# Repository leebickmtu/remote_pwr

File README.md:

Remote Power (RPi HAT)
=========================
Remotely query/change the power state of a computer from an always on, low power Raspberry Pi.

Intended to be used over SSH to control the power state of a desktop computer.

Includes EAGLE board schematic for a RPi Zero HAT which the computer's front panel header connect to. And python scripts which can then be executed on the RPi to query/change the power state of the connected computer.

EAGLE board and schematic
--------

Python script use
--------
```bash
# Query the power state (returns 'sleep', 'on', 'off')
./remote_pwr state

# "Push" the power or reset buttons
./remote_pwr pulse pwr
./remote_pwr pulse rst

# "Hold" the power button
./remote_pwr hold pwr
```

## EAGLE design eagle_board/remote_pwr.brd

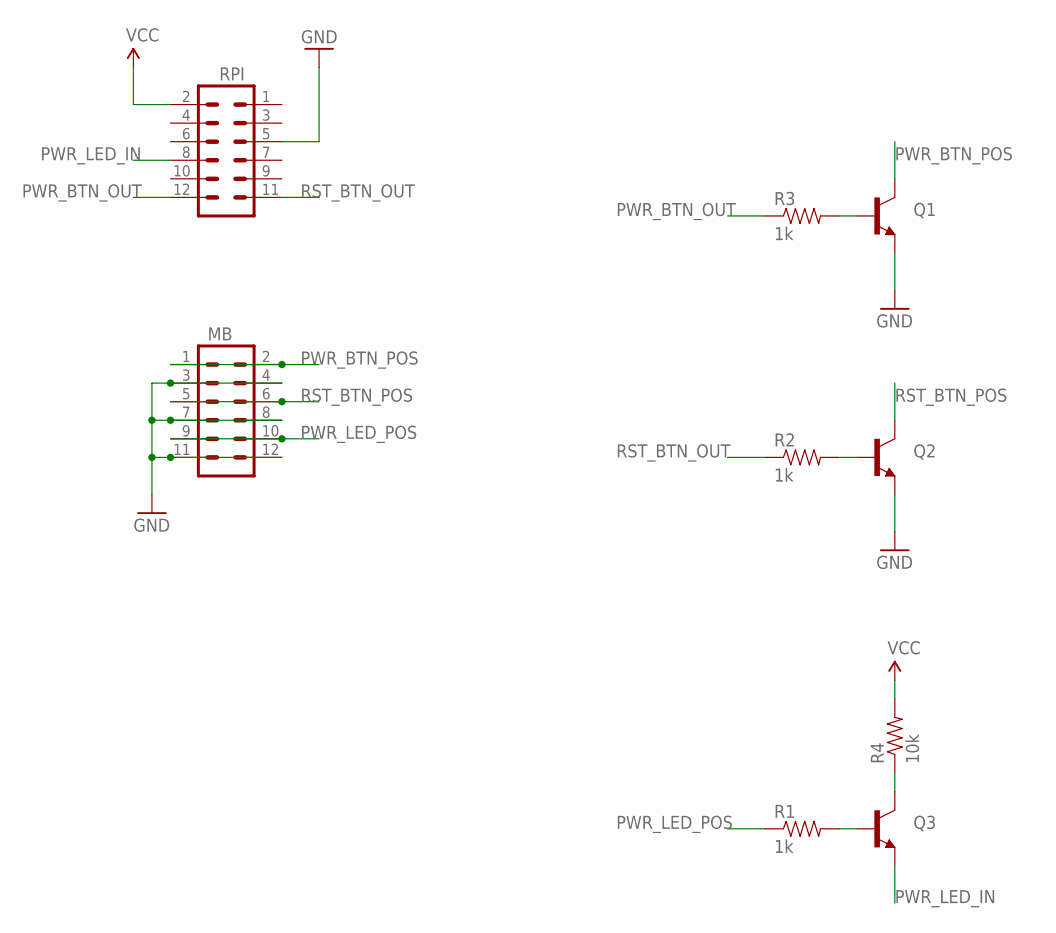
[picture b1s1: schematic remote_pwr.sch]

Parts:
MB: M06X2PTH_FEMALE; 2X6
Q1, Q2, Q3: TRANSISTOR_NPNTO-92-AMMO; TO-92-AMMO
R1, R2, R3: 1k; AXIAL-0.3
R4: 10k; AXIAL-0.3
RPI: M06X2PTH_FEMALE; 2X6

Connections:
GND: MB.3, MB.4, MB.7, MB.8, MB.11, MB.12, Q1.1 (E), Q2.1 (E), RPI.5
unnamed: Q3.3 (C), R4.P$1 (1)
unnamed: Q1.2 (B), R3.P$2 (2)
unnamed: Q2.2 (B), R2.P$2 (2)
unnamed: Q3.2 (B), R1.P$2 (2)
PWR_BTN_OUT: R3.P$1 (1), RPI.12
PWR_BTN_POS: MB.1, MB.2, Q1.3 (C)
PWR_LED_IN: Q3.1 (E), RPI.8
PWR_LED_POS: MB.9, MB.10, R1.P$1 (1)
RST_BTN_OUT: R2.P$1 (1), RPI.11
RST_BTN_POS: MB.5, MB.6, Q2.3 (C)
VCC: R4.P$2 (2), RPI.2

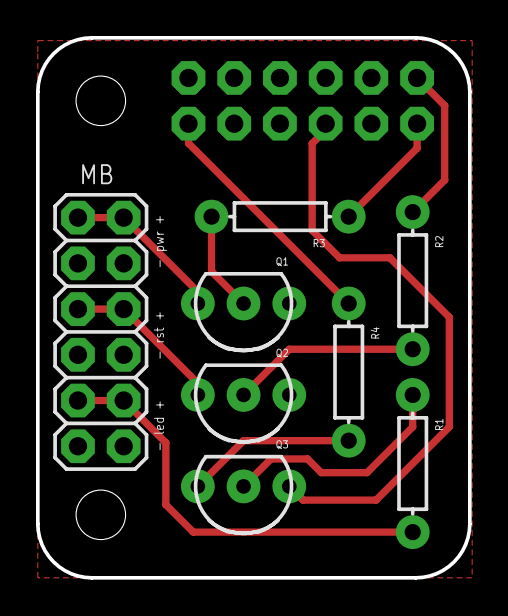
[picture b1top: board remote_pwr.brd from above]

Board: 2 copper layers, 24.0 x 30.0 mm, 9 parts (1 on the bottom side), 12 nets.

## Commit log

2016-07-27 Add project files
2016-07-27 Add image of EAGLE schematic and board
2016-07-27 Update README.md
    Note that the RPi HAT footprint is designed for the RPi Zero.
2016-07-27 Upload images for README
2016-07-28 Update EAGLE board
    Change board to have all traces and ground plane on single side.
2016-07-28 Update EAGLE board
    Revert to old layout but still move traces to single side.
2016-09-21 Update LICENSE
    Switch from GPL to Unlicense going forward.
2023-03-01 python 3 updates

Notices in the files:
parts and their libraries:
SparkFun-Connectors: Licensing: Creative Commons ShareAlike 4.0 International - https://creativecommons.org/licenses/by-sa/4.0
